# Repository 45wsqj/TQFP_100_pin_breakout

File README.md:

# TQFP_100_pin_breakout
A Breakout board suitable for TQFP packages of multiple sizes. For both 0.8 and 0.5 mm of pin spacing.

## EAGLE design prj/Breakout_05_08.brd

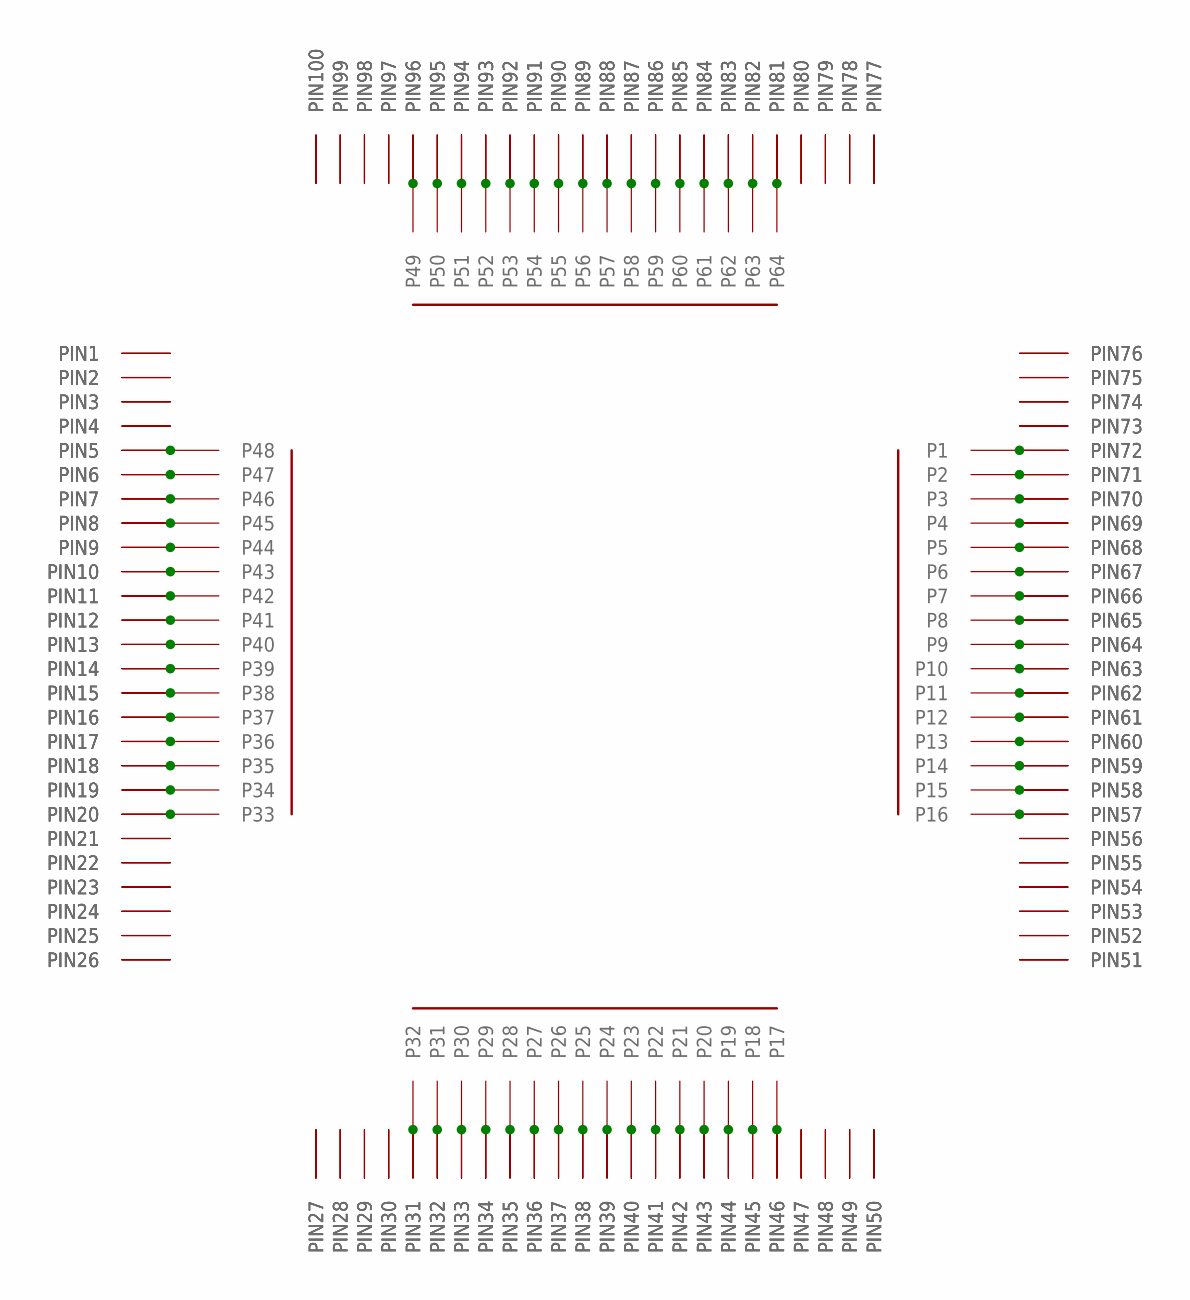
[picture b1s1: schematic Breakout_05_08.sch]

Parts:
U$1: OUTTER_PADS_100PIN; TQFP_100_PIN_DIN
U$2: SMT_64PIN_R; TQFP_SMT_08MM
U$3: SMT_100PIN; TQFP_SMT_05MM

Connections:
unnamed: U$1.P$157 (PIN57), U$2.P$16 (P16), U$3.P$57 (PIN57)
unnamed: U$1.P$158 (PIN58), U$2.P$15 (P15), U$3.P$58 (PIN58)
unnamed: U$1.P$159 (PIN59), U$2.P$14 (P14), U$3.P$59 (PIN59)
unnamed: U$1.P$160 (PIN60), U$2.P$13 (P13), U$3.P$60 (PIN60)
unnamed: U$1.P$161 (PIN61), U$2.P$12 (P12), U$3.P$61 (PIN61)
unnamed: U$1.P$162 (PIN62), U$2.P$11 (P11), U$3.P$62 (PIN62)
unnamed: U$1.P$163 (PIN63), U$2.P$10 (P10), U$3.P$63 (PIN63)
unnamed: U$1.P$164 (PIN64), U$2.P$9 (P9), U$3.P$64 (PIN64)
unnamed: U$1.P$165 (PIN65), U$2.P$8 (P8), U$3.P$65 (PIN65)
unnamed: U$1.P$166 (PIN66), U$2.P$7 (P7), U$3.P$66 (PIN66)
unnamed: U$1.P$167 (PIN67), U$2.P$6 (P6), U$3.P$67 (PIN67)
unnamed: U$1.P$168 (PIN68), U$2.P$5 (P5), U$3.P$68 (PIN68)
unnamed: U$1.P$169 (PIN69), U$2.P$4 (P4), U$3.P$69 (PIN69)
unnamed: U$1.P$170 (PIN70), U$2.P$3 (P3), U$3.P$70 (PIN70)
unnamed: U$1.P$171 (PIN71), U$2.P$2 (P2), U$3.P$71 (PIN71)
unnamed: U$1.P$172 (PIN72), U$2.P$1 (P1), U$3.P$72 (PIN72)
unnamed: U$1.P$146 (PIN46), U$2.P$17 (P17), U$3.P$46 (PIN46)
unnamed: U$1.P$145 (PIN45), U$2.P$18 (P18), U$3.P$45 (PIN45)
unnamed: U$1.P$144 (PIN44), U$2.P$19 (P19), U$3.P$44 (PIN44)
unnamed: U$1.P$143 (PIN43), U$2.P$20 (P20), U$3.P$43 (PIN43)
unnamed: U$1.P$142 (PIN42), U$2.P$21 (P21), U$3.P$42 (PIN42)
unnamed: U$1.P$141 (PIN41), U$2.P$22 (P22), U$3.P$41 (PIN41)
unnamed: U$1.P$140 (PIN40), U$2.P$23 (P23), U$3.P$40 (PIN40)
unnamed: U$1.P$139 (PIN39), U$2.P$24 (P24), U$3.P$39 (PIN39)
unnamed: U$1.P$138 (PIN38), U$2.P$25 (P25), U$3.P$38 (PIN38)
unnamed: U$1.P$137 (PIN37), U$2.P$27 (P26), U$3.P$37 (PIN37)
unnamed: U$1.P$136 (PIN36), U$2.P$28 (P27), U$3.P$36 (PIN36)
unnamed: U$1.P$135 (PIN35), U$2.P$29 (P28), U$3.P$35 (PIN35)
unnamed: U$1.P$134 (PIN34), U$2.P$30 (P29), U$3.P$34 (PIN34)
unnamed: U$1.P$133 (PIN33), U$2.P$31 (P30), U$3.P$33 (PIN33)
unnamed: U$1.P$132 (PIN32), U$2.P$32 (P31), U$3.P$32 (PIN32)
unnamed: U$1.P$131 (PIN31), U$2.P$33 (P32), U$3.P$31 (PIN31)
unnamed: U$1.P$120 (PIN20), U$2.P$34 (P33), U$3.P$20 (PIN20)
unnamed: U$1.P$119 (PIN19), U$2.P$35 (P34), U$3.P$19 (PIN19)
unnamed: U$1.P$118 (PIN18), U$2.P$36 (P35), U$3.P$18 (PIN18)
unnamed: U$1.P$117 (PIN17), U$2.P$37 (P36), U$3.P$17 (PIN17)
unnamed: U$1.P$116 (PIN16), U$2.P$38 (P37), U$3.P$16 (PIN16)
unnamed: U$1.P$115 (PIN15), U$2.P$39 (P38), U$3.P$15 (PIN15)
unnamed: U$1.P$114 (PIN14), U$2.P$40 (P39), U$3.P$14 (PIN14)
unnamed: U$1.P$113 (PIN13), U$2.P$41 (P40), U$3.P$13 (PIN13)
unnamed: U$1.P$112 (PIN12), U$2.P$42 (P41), U$3.P$12 (PIN12)
unnamed: U$1.P$111 (PIN11), U$2.P$43 (P42), U$3.P$11 (PIN11)
unnamed: U$1.P$110 (PIN10), U$2.P$44 (P43), U$3.P$10 (PIN10)
unnamed: U$1.P$109 (PIN9), U$2.P$45 (P44), U$3.P$9 (PIN9)
unnamed: U$1.P$108 (PIN8), U$2.P$46 (P45), U$3.P$8 (PIN8)
unnamed: U$1.P$107 (PIN7), U$2.P$47 (P46), U$3.P$7 (PIN7)
unnamed: U$1.P$106 (PIN6), U$2.P$48 (P47), U$3.P$6 (PIN6)
unnamed: U$1.P$105 (PIN5), U$2.P$49 (P48), U$3.P$5 (PIN5)
unnamed: U$1.P$196 (PIN96), U$2.P$50 (P49), U$3.P$96 (PIN96)
unnamed: U$1.P$195 (PIN95), U$2.P$51 (P50), U$3.P$95 (PIN95)
unnamed: U$1.P$194 (PIN94), U$2.P$52 (P51), U$3.P$94 (PIN94)
unnamed: U$1.P$193 (PIN93), U$2.P$53 (P52), U$3.P$93 (PIN93)
unnamed: U$1.P$192 (PIN92), U$2.P$54 (P53), U$3.P$92 (PIN92)
unnamed: U$1.P$191 (PIN91), U$2.P$55 (P54), U$3.P$91 (PIN91)
unnamed: U$1.P$190 (PIN90), U$2.P$56 (P55), U$3.P$90 (PIN90)
unnamed: U$1.P$189 (PIN89), U$2.P$57 (P56), U$3.P$89 (PIN89)
unnamed: U$1.P$188 (PIN88), U$2.P$58 (P57), U$3.P$88 (PIN88)
unnamed: U$1.P$187 (PIN87), U$2.P$59 (P58), U$3.P$87 (PIN87)
unnamed: U$1.P$186 (PIN86), U$2.P$60 (P59), U$3.P$86 (PIN86)
unnamed: U$1.P$185 (PIN85), U$2.P$61 (P60), U$3.P$85 (PIN85)
unnamed: U$1.P$184 (PIN84), U$2.P$62 (P61), U$3.P$84 (PIN84)
unnamed: U$1.P$183 (PIN83), U$2.P$63 (P62), U$3.P$83 (PIN83)
unnamed: U$1.P$182 (PIN82), U$2.P$64 (P63), U$3.P$82 (PIN82)
unnamed: U$1.P$181 (PIN81), U$2.P$65 (P64), U$3.P$81 (PIN81)
unnamed: U$1.P$101 (PIN1), U$3.P$1 (PIN1)
unnamed: U$1.P$102 (PIN2), U$3.P$2 (PIN2)
unnamed: U$1.P$103 (PIN3), U$3.P$3 (PIN3)
unnamed: U$1.P$104 (PIN4), U$3.P$4 (PIN4)
unnamed: U$1.P$121 (PIN21), U$3.P$21 (PIN21)
unnamed: U$1.P$122 (PIN22), U$3.P$22 (PIN22)
unnamed: U$1.P$123 (PIN23), U$3.P$23 (PIN23)
unnamed: U$1.P$124 (PIN24), U$3.P$24 (PIN24)
unnamed: U$1.P$125 (PIN25), U$3.P$25 (PIN25)
unnamed: U$1.P$126 (PIN26), U$3.P$26 (PIN26)
unnamed: U$1.P$127 (PIN27), U$3.P$27 (PIN27)
unnamed: U$1.P$128 (PIN28), U$3.P$28 (PIN28)
unnamed: U$1.P$129 (PIN29), U$3.P$29 (PIN29)
unnamed: U$1.P$130 (PIN30), U$3.P$30 (PIN30)
unnamed: U$1.P$147 (PIN47), U$3.P$47 (PIN47)
unnamed: U$1.P$148 (PIN48), U$3.P$48 (PIN48)
unnamed: U$1.P$149 (PIN49), U$3.P$49 (PIN49)
unnamed: U$1.P$150 (PIN50), U$3.P$50 (PIN50)
unnamed: U$1.P$151 (PIN51), U$3.P$51 (PIN51)
unnamed: U$1.P$152 (PIN52), U$3.P$52 (PIN52)
unnamed: U$1.P$153 (PIN53), U$3.P$53 (PIN53)
unnamed: U$1.P$154 (PIN54), U$3.P$54 (PIN54)
unnamed: U$1.P$155 (PIN55), U$3.P$55 (PIN55)
unnamed: U$1.P$156 (PIN56), U$3.P$56 (PIN56)
unnamed: U$1.P$173 (PIN73), U$3.P$73 (PIN73)
unnamed: U$1.P$174 (PIN74), U$3.P$74 (PIN74)
unnamed: U$1.P$175 (PIN75), U$3.P$75 (PIN75)
unnamed: U$1.P$176 (PIN76), U$3.P$76 (PIN76)
unnamed: U$1.P$177 (PIN77), U$3.P$77 (PIN77)
unnamed: U$1.P$178 (PIN78), U$3.P$78 (PIN78)
unnamed: U$1.P$179 (PIN79), U$3.P$79 (PIN79)
unnamed: U$1.P$180 (PIN80), U$3.P$80 (PIN80)
unnamed: U$1.P$197 (PIN97), U$3.P$97 (PIN97)
unnamed: U$1.P$198 (PIN98), U$3.P$98 (PIN98)
unnamed: U$1.P$199 (PIN99), U$3.P$99 (PIN99)
unnamed: U$1.P$200 (PIN100), U$3.P$100 (PIN100)

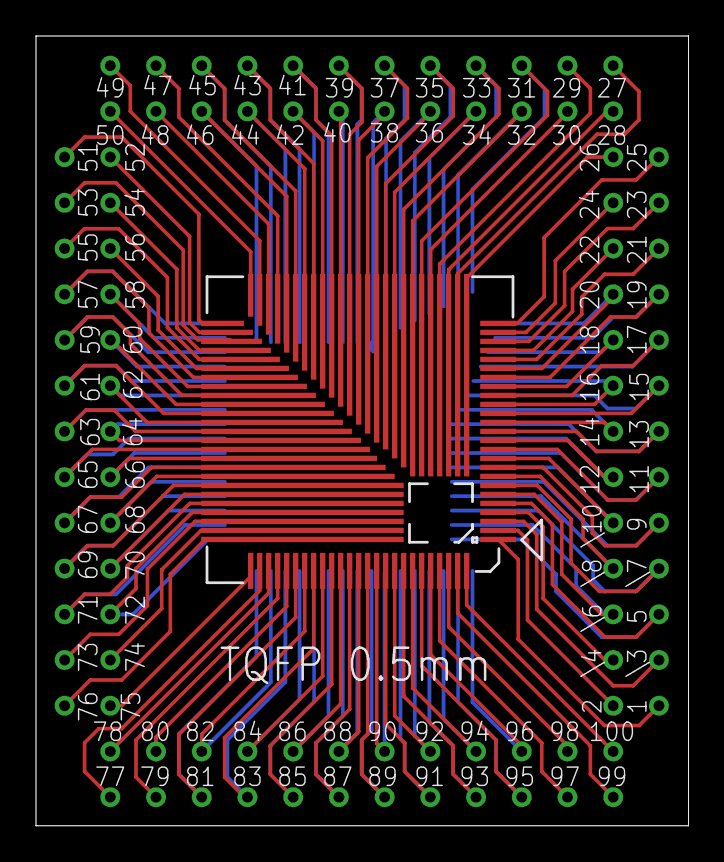
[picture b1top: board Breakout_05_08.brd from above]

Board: 2 copper layers, 36.2 x 43.9 mm, 3 parts (1 on the bottom side), 100 nets.

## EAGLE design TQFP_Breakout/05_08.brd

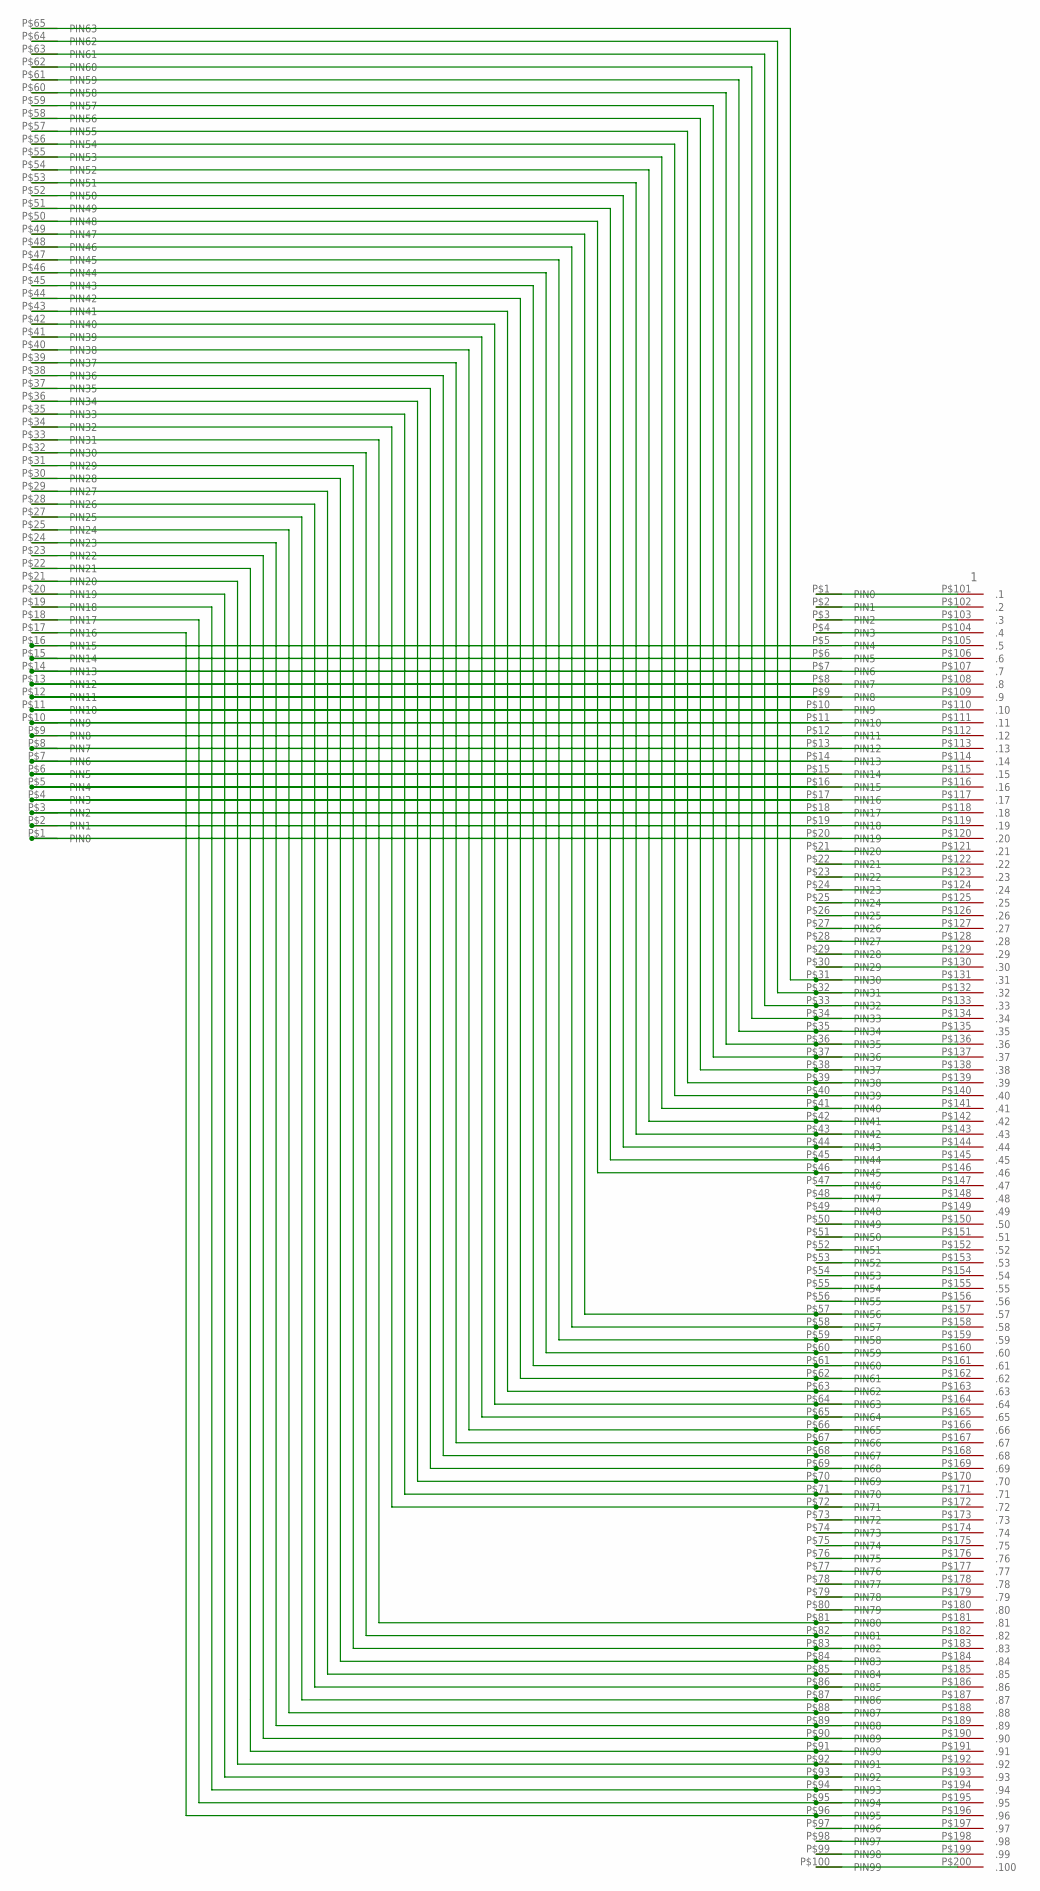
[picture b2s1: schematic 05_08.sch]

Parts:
U$1: TQFP_100_PIN_1; TQFP_100PIN_PCB_1
U$2: TQFP_100_PIN_2; TQFP_100PIN_PCB_2
U$3: TQFP_64_PIN; TQFP_100PIN_PCB_08

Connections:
1: U$1.P$1 (PIN0), U$2.P$101 (.1)
unnamed: U$1.P$2 (PIN1), U$2.P$102 (.2)
unnamed: U$1.P$3 (PIN2), U$2.P$103 (.3)
unnamed: U$1.P$4 (PIN3), U$2.P$104 (.4)
unnamed: U$1.P$7 (PIN6), U$2.P$107 (.7), U$3.P$14 (PIN13)
unnamed: U$1.P$6 (PIN5), U$2.P$106 (.6), U$3.P$15 (PIN14)
unnamed: U$1.P$8 (PIN7), U$2.P$108 (.8), U$3.P$13 (PIN12)
unnamed: U$1.P$9 (PIN8), U$2.P$109 (.9), U$3.P$12 (PIN11)
unnamed: U$1.P$10 (PIN9), U$2.P$110 (.10), U$3.P$11 (PIN10)
unnamed: U$1.P$30 (PIN29), U$2.P$130 (.30)
unnamed: U$1.P$11 (PIN10), U$2.P$111 (.11), U$3.P$10 (PIN9)
unnamed: U$1.P$12 (PIN11), U$2.P$112 (.12), U$3.P$9 (PIN8)
unnamed: U$1.P$13 (PIN12), U$2.P$113 (.13), U$3.P$8 (PIN7)
unnamed: U$1.P$14 (PIN13), U$2.P$114 (.14), U$3.P$7 (PIN6)
unnamed: U$1.P$15 (PIN14), U$2.P$115 (.15), U$3.P$6 (PIN5)
unnamed: U$1.P$16 (PIN15), U$2.P$116 (.16), U$3.P$5 (PIN4)
unnamed: U$1.P$17 (PIN16), U$2.P$117 (.17), U$3.P$4 (PIN3)
unnamed: U$1.P$18 (PIN17), U$2.P$118 (.18), U$3.P$3 (PIN2)
unnamed: U$1.P$19 (PIN18), U$2.P$119 (.19), U$3.P$2 (PIN1)
unnamed: U$1.P$20 (PIN19), U$2.P$120 (.20), U$3.P$1 (PIN0)
unnamed: U$1.P$21 (PIN20), U$2.P$121 (.21)
unnamed: U$1.P$22 (PIN21), U$2.P$122 (.22)
unnamed: U$1.P$23 (PIN22), U$2.P$123 (.23)
unnamed: U$1.P$24 (PIN23), U$2.P$124 (.24)
unnamed: U$1.P$25 (PIN24), U$2.P$125 (.25)
unnamed: U$1.P$26 (PIN25), U$2.P$126 (.26)
unnamed: U$1.P$27 (PIN26), U$2.P$127 (.27)
unnamed: U$1.P$28 (PIN27), U$2.P$128 (.28)
unnamed: U$1.P$29 (PIN28), U$2.P$129 (.29)
unnamed: U$1.P$32 (PIN31), U$2.P$132 (.32), U$3.P$64 (PIN62)
unnamed: U$1.P$33 (PIN32), U$2.P$133 (.33), U$3.P$63 (PIN61)
unnamed: U$1.P$34 (PIN33), U$2.P$134 (.34), U$3.P$62 (PIN60)
unnamed: U$1.P$35 (PIN34), U$2.P$135 (.35), U$3.P$61 (PIN59)
unnamed: U$1.P$36 (PIN35), U$2.P$136 (.36), U$3.P$60 (PIN58)
unnamed: U$1.P$37 (PIN36), U$2.P$137 (.37), U$3.P$59 (PIN57)
unnamed: U$1.P$38 (PIN37), U$2.P$138 (.38), U$3.P$58 (PIN56)
unnamed: U$1.P$39 (PIN38), U$2.P$139 (.39), U$3.P$57 (PIN55)
unnamed: U$1.P$40 (PIN39), U$2.P$140 (.40), U$3.P$56 (PIN54)
unnamed: U$1.P$41 (PIN40), U$2.P$141 (.41), U$3.P$55 (PIN53)
unnamed: U$1.P$42 (PIN41), U$2.P$142 (.42), U$3.P$54 (PIN52)
unnamed: U$1.P$43 (PIN42), U$2.P$143 (.43), U$3.P$53 (PIN51)
unnamed: U$1.P$44 (PIN43), U$2.P$144 (.44), U$3.P$52 (PIN50)
unnamed: U$1.P$45 (PIN44), U$2.P$145 (.45), U$3.P$51 (PIN49)
unnamed: U$1.P$46 (PIN45), U$2.P$146 (.46), U$3.P$50 (PIN48)
unnamed: U$1.P$47 (PIN46), U$2.P$147 (.47)
unnamed: U$1.P$48 (PIN47), U$2.P$148 (.48)
unnamed: U$1.P$49 (PIN48), U$2.P$149 (.49)
unnamed: U$1.P$50 (PIN49), U$2.P$150 (.50)
unnamed: U$1.P$51 (PIN50), U$2.P$151 (.51)
unnamed: U$1.P$52 (PIN51), U$2.P$152 (.52)
unnamed: U$1.P$53 (PIN52), U$2.P$153 (.53)
unnamed: U$1.P$54 (PIN53), U$2.P$154 (.54)
unnamed: U$1.P$55 (PIN54), U$2.P$155 (.55)
unnamed: U$1.P$56 (PIN55), U$2.P$156 (.56)
unnamed: U$1.P$57 (PIN56), U$2.P$157 (.57), U$3.P$49 (PIN47)
unnamed: U$1.P$58 (PIN57), U$2.P$158 (.58), U$3.P$48 (PIN46)
unnamed: U$1.P$59 (PIN58), U$2.P$159 (.59), U$3.P$47 (PIN45)
unnamed: U$1.P$60 (PIN59), U$2.P$160 (.60), U$3.P$46 (PIN44)
unnamed: U$1.P$61 (PIN60), U$2.P$161 (.61), U$3.P$45 (PIN43)
unnamed: U$1.P$62 (PIN61), U$2.P$162 (.62), U$3.P$44 (PIN42)
unnamed: U$1.P$63 (PIN62), U$2.P$163 (.63), U$3.P$43 (PIN41)
unnamed: U$1.P$64 (PIN63), U$2.P$164 (.64), U$3.P$42 (PIN40)
unnamed: U$1.P$65 (PIN64), U$2.P$165 (.65), U$3.P$41 (PIN39)
unnamed: U$1.P$66 (PIN65), U$2.P$166 (.66), U$3.P$40 (PIN38)
unnamed: U$1.P$67 (PIN66), U$2.P$167 (.67), U$3.P$39 (PIN37)
unnamed: U$1.P$68 (PIN67), U$2.P$168 (.68), U$3.P$38 (PIN36)
unnamed: U$1.P$69 (PIN68), U$2.P$169 (.69), U$3.P$37 (PIN35)
unnamed: U$1.P$70 (PIN69), U$2.P$170 (.70), U$3.P$36 (PIN34)
unnamed: U$1.P$71 (PIN70), U$2.P$171 (.71), U$3.P$35 (PIN33)
unnamed: U$1.P$72 (PIN71), U$2.P$172 (.72), U$3.P$34 (PIN32)
unnamed: U$1.P$73 (PIN72), U$2.P$173 (.73)
unnamed: U$1.P$74 (PIN73), U$2.P$174 (.74)
unnamed: U$1.P$75 (PIN74), U$2.P$175 (.75)
unnamed: U$1.P$76 (PIN75), U$2.P$176 (.76)
unnamed: U$1.P$77 (PIN76), U$2.P$177 (.77)
unnamed: U$1.P$78 (PIN77), U$2.P$178 (.78)
unnamed: U$1.P$79 (PIN78), U$2.P$179 (.79)
unnamed: U$1.P$80 (PIN79), U$2.P$180 (.80)
unnamed: U$1.P$81 (PIN80), U$2.P$181 (.81), U$3.P$33 (PIN31)
unnamed: U$1.P$82 (PIN81), U$2.P$182 (.82), U$3.P$32 (PIN30)
unnamed: U$1.P$83 (PIN82), U$2.P$183 (.83), U$3.P$31 (PIN29)
unnamed: U$1.P$84 (PIN83), U$2.P$184 (.84), U$3.P$30 (PIN28)
unnamed: U$1.P$85 (PIN84), U$2.P$185 (.85), U$3.P$29 (PIN27)
unnamed: U$1.P$86 (PIN85), U$2.P$186 (.86), U$3.P$28 (PIN26)
unnamed: U$1.P$87 (PIN86), U$2.P$187 (.87), U$3.P$27 (PIN25)
unnamed: U$1.P$88 (PIN87), U$2.P$188 (.88), U$3.P$25 (PIN24)
unnamed: U$1.P$89 (PIN88), U$2.P$189 (.89), U$3.P$24 (PIN23)
unnamed: U$1.P$90 (PIN89), U$2.P$190 (.90), U$3.P$23 (PIN22)
unnamed: U$1.P$91 (PIN90), U$2.P$191 (.91), U$3.P$22 (PIN21)
unnamed: U$1.P$92 (PIN91), U$2.P$192 (.92), U$3.P$21 (PIN20)
unnamed: U$1.P$93 (PIN92), U$2.P$193 (.93), U$3.P$20 (PIN19)
unnamed: U$1.P$94 (PIN93), U$2.P$194 (.94), U$3.P$19 (PIN18)
unnamed: U$1.P$95 (PIN94), U$2.P$195 (.95), U$3.P$18 (PIN17)
unnamed: U$1.P$96 (PIN95), U$2.P$196 (.96), U$3.P$17 (PIN16)
unnamed: U$1.P$97 (PIN96), U$2.P$197 (.97)
unnamed: U$1.P$98 (PIN97), U$2.P$198 (.98)
unnamed: U$1.P$99 (PIN98), U$2.P$199 (.99)
unnamed: U$1.P$100 (PIN99), U$2.P$200 (.100)
unnamed: U$1.P$31 (PIN30), U$2.P$131 (.31), U$3.P$65 (PIN63)
unnamed: U$1.P$5 (PIN4), U$2.P$105 (.5), U$3.P$16 (PIN15)

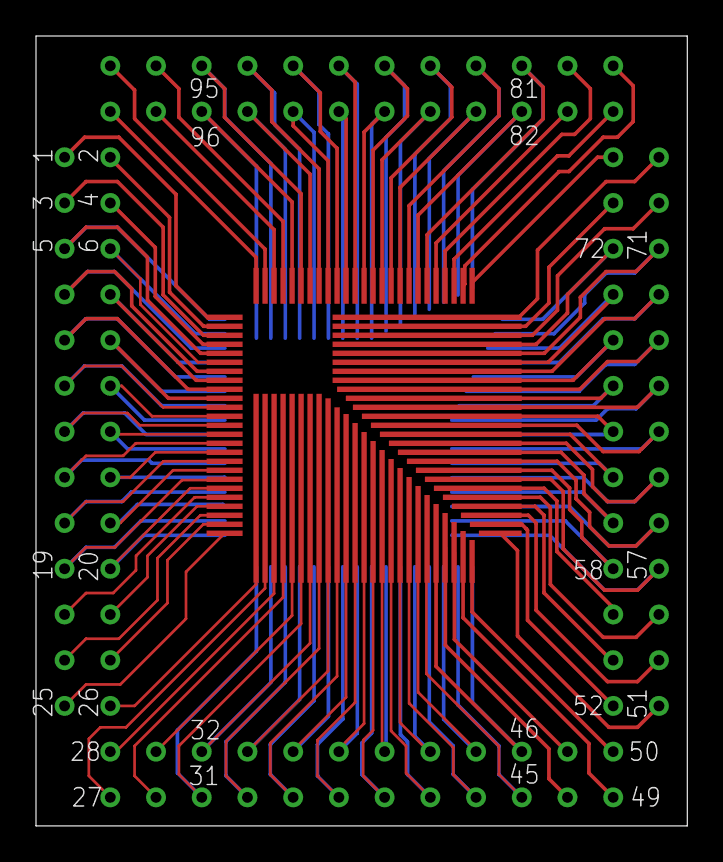
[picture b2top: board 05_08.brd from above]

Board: 2 copper layers, 36.2 x 43.9 mm, 3 parts (1 on the bottom side), 100 nets.
